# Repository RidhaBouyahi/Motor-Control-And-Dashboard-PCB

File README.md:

# Motor Control And Dashboard PCB
 
 This Dashboard PCB is developed to get data (position,temperature...) from sensors, control actuators and Dc Motor direction  and speed control using PWM .
All of these with the use of a touch panel screen connected to the board to make it easy for the user to operate and command everything with a simple touch.
The dimension of the PCB is 82.5*64 (mm)
It features : 
* Built-in H Bridge for speed and direction control.
* Reverse Current Protection Circuit.
* AVR-SPI Programmer. 
* UART for serial communications. 
* 4 digital and 5 Analog pins.

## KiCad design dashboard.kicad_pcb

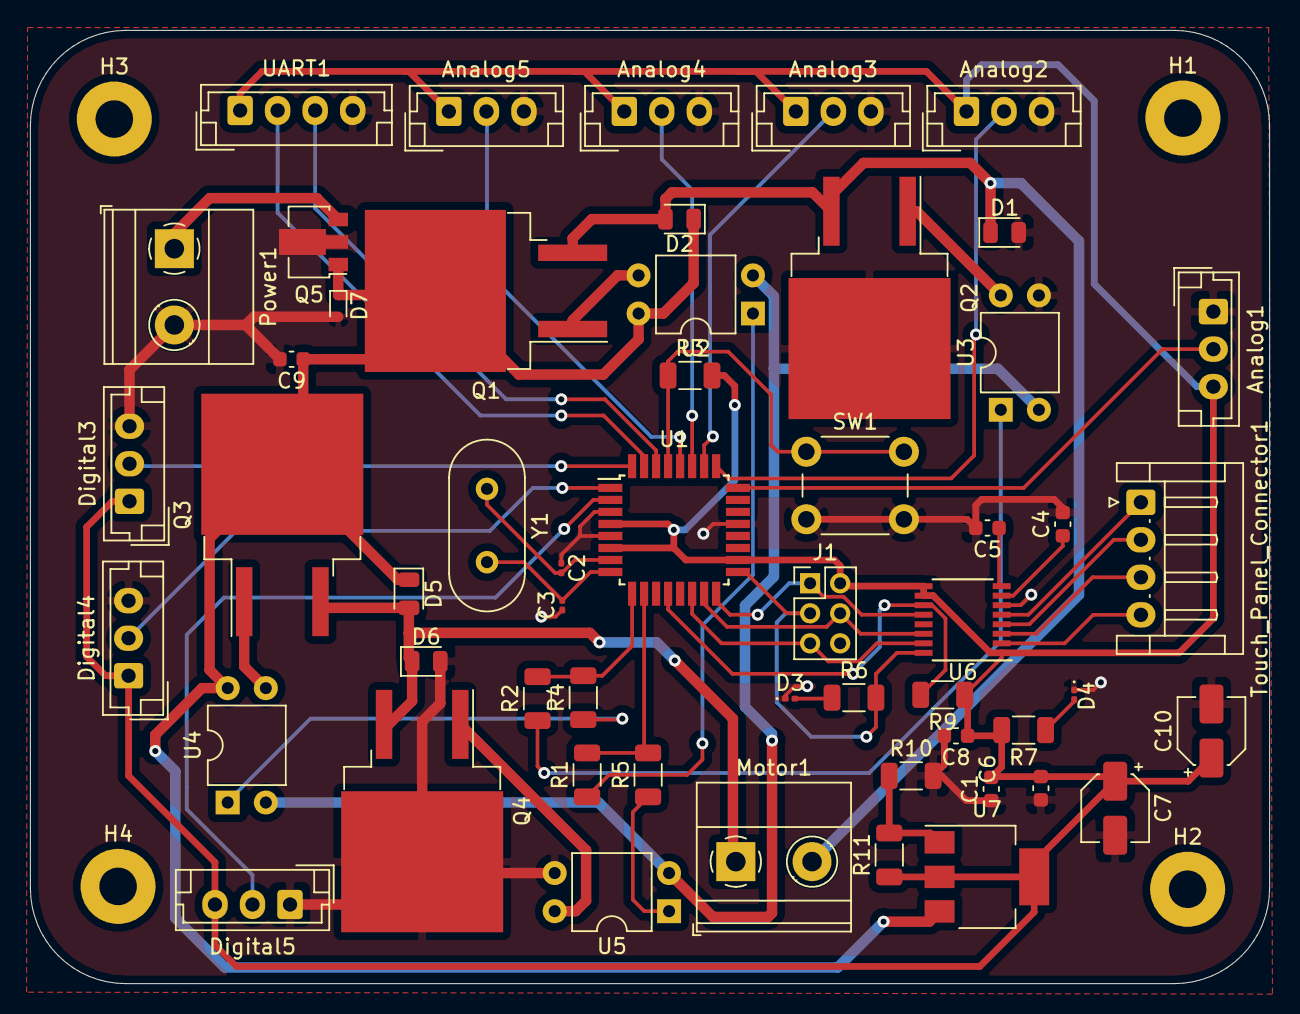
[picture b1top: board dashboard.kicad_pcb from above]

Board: 2 copper layers, 82.5 x 63.5 mm, 58 parts (0 on the bottom side), 44 nets.

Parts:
Analog1: ap1; JST_EH_B3B-EH-A_1x03_P2.50mm_Vertical
Analog2: ap2; JST_EH_B3B-EH-A_1x03_P2.50mm_Vertical
Analog3: ap3; JST_EH_B3B-EH-A_1x03_P2.50mm_Vertical
Analog4: ap4; JST_EH_B3B-EH-A_1x03_P2.50mm_Vertical
Analog5: ap5; JST_EH_B3B-EH-A_1x03_P2.50mm_Vertical
C1, C4, C5, C6, C8: 100nF; C_0603_1608Metric
C2, C3: 23pF; C_0201_0603Metric
C7: 10uF; CP_Elec_4x3
C9: 110nF; C_0603_1608Metric
C10: 180uF; CP_Elec_4x3
D1, D2, D5, D6: 1N4001; D_0805_2012Metric
D3, D4: LED; LED_0201_0603Metric
D7: D_Zener_Small; D_SC-80
Digital3: dp3; JST_EH_B3B-EH-A_1x03_P2.50mm_Vertical
Digital4: dp4; JST_EH_B3B-EH-A_1x03_P2.50mm_Vertical
Digital5: dp5; JST_EH_B3B-EH-A_1x03_P2.50mm_Vertical
H1, H2, H3, H4: MountingHole; MountingHole_2.5mm_Pad
J1: AVR-ISP-6; PinHeader_2x03_P2.00mm_Vertical
Motor1: Motor; TerminalBlock_Phoenix_MKDS-1,5-2-5.08_1x02_P5.08mm_Horizont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
Power1: Power; TerminalBlock_Phoenix_MKDS-1,5-2-5.08_1x02_P5.08mm_Horizont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
Q1, Q3: TIP122; TO-263-2
Q2, Q4: TIP127; TO-263-2
Q5: TP0610L; SOT-89-3
R1, R2, R4, R5: 1K2; R_1206_3216Metric
R3, R10: 10k; R_1206_3216Metric
R6, R7: 1k; R_1206_3216Metric
R9: 100k; R_1206_3216Metric
R11: 3k3; R_1206_3216Metric
SW1: SW_Push; SW_PUSH_6mm
Touch_Panel_Connector1: Touch Panel; JST_EH_S4B-EH_1x04_P2.50mm_Horizontal
U1: ATmega328-AU; TQFP-32_7x7mm_P0.8mm
U2, U3, U4, U5: EL817; DIP-4_W7.62mm
U6: ADS7843E; SSOP-16_3.9x4.9mm_P0.635mm
U7: LM317_SOT-223; SOT-223-3_TabPin2
UART1: UART; JST_EH_B4B-EH-A_1x04_P2.50mm_Vertical
Y1: 16MHz; Crystal_HC49-4H_Vertical

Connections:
+5: Analog1.3, Analog2.1, Analog3.1, Analog4.1, Analog5.1, C1.2, C6.1, C7.1, C8.1, C10.1, Digital3.1, Digital4.1, Digital5.3, J1.2, R3.2, R7.2, R9.1, R11.1, U1.4, U1.6, U1.18, U6.1, U6.9, U6.10, U7.2, UART1.1
+24V: C9.1, D2.1, D5.1, D7.1, Q1.2, Q3.2, Q5.1, U2.4, U4.4, U7.3
AP1: Analog1.2, U1.24
AP2: Analog2.2, U1.25
AP3: Analog3.2, U1.26
AP4: Analog4.2, U1.27
AP5: Analog5.2, U1.28
CLK: J1.3, R6.2, U1.17, U6.16
DP3: Digital3.2, U1.32
DP4: Digital4.2, U1.1
DP5: Digital5.2, U1.2
GND: Analog1.1, Analog2.3, Analog3.3, Analog4.3, Analog5.3, C1.1, C2.1, C3.1, C4.2, C5.2, C6.2, C7.2, C8.2, C9.2, C10.2, D1.2, D3.1, D4.1, D6.2, D7.2, Digital3.3, Digital4.3, Digital5.1, J1.6, Power1.2, Q2.2, Q4.2, Q5.2, R10.2, SW1.2, U1.3, U1.5, U1.21, U3.3, U5.3, U6.6, UART1.4
GNDPWR: U2.2, U3.2, U4.2, U5.2
INTERRUPT: R9.2, U1.12, U6.11
M+: D1.1, D2.2, Motor1.2, Q1.3, Q2.3
M-: D5.2, D6.1, Motor1.1, Q3.3, Q4.3
MISO: J1.1, U1.16, U6.12
MOSI: J1.4, U1.15, U6.14
unnamed: C2.2, U1.7, Y1.1
unnamed: C3.2, U1.8, Y1.2
unnamed: C4.1, U6.7
unnamed: C5.1, U6.8
unnamed: D3.2, R6.1
unnamed: D4.2, R7.1
unnamed: Power1.1, Q5.3
unnamed: Q1.1, U2.3
unnamed: Q2.1, U3.4
unnamed: Q3.1, U4.3
unnamed: Q4.1, U5.4
unnamed: R1.1, U2.1
unnamed: R2.1, U3.1
unnamed: R4.1, U4.1
unnamed: R5.1, U5.1
unnamed: R10.1, R11.2, U7.1
PWM0: R1.2, R5.2, U1.10
PWM1: R2.2, R4.2, U1.9
RST: R3.1, SW1.1, U1.29
RX: U1.30, UART1.3
TX: U1.31, UART1.2
X+: Touch_Panel_Connector1.4, U6.2
X-: Touch_Panel_Connector1.2, U6.4
Y+: Touch_Panel_Connector1.3, U6.3
Y-: Touch_Panel_Connector1.1, U6.5
~SS: J1.5, U1.14, U6.15

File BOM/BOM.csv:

Id;Symbol;Reference;Units;Part Value
1;UART1;JST_EH_B4B-EH-A_1x04_P2.50mm_Vertical;1;UART
2;H4,H3,H2,H1;MountingHole_2.5mm_Pad;4;MountingHole
3;Analog5;JST_EH_B3B-EH-A_1x03_P2.50mm_Vertical;1;ap5
4;Digital5;JST_EH_B3B-EH-A_1x03_P2.50mm_Vertical;1;dp5
5;Analog4;JST_EH_B3B-EH-A_1x03_P2.50mm_Vertical;1;ap4
6;Digital4;JST_EH_B3B-EH-A_1x03_P2.50mm_Vertical;1;dp4
7;Analog3;JST_EH_B3B-EH-A_1x03_P2.50mm_Vertical;1;ap3
8;Digital3;JST_EH_B3B-EH-A_1x03_P2.50mm_Vertical;1;dp3
9;Analog2;JST_EH_B3B-EH-A_1x03_P2.50mm_Vertical;1;ap2
10;Analog1;JST_EH_B3B-EH-A_1x03_P2.50mm_Vertical;1;ap1
11;Y1;Crystal_HC49-4H_Vertical;1;16MHz
12;U7;SOT-223-3_TabPin2;1;LM317_SOT-223
13;U6;SSOP-16_3.9x4.9mm_P0.635mm;1;ADS7843E
14;U5,U4,U3,U2;DIP-4_W7.62mm;4;EL817
15;U1;TQFP-32_7x7mm_P0.8mm;1;ATmega328-AU
16;SW1;SW_PUSH_6mm;1;SW_Push
17;R11;R_1206_3216Metric;1;3k3
18;R10,R3;R_1206_3216Metric;2;10k
19;R9;R_1206_3216Metric;1;100k
20;R7,R6;R_1206_3216Metric;2;1k
21;R5,R4,R2,R1;R_1206_3216Metric;4;1K2
22;Q5;SOT-89-3;1;TP0610L
23;Q4,Q2;TO-263-2;2;TIP127
24;Q3,Q1;TO-263-2;2;TIP122
25;Touch_Panel_Connector1;JST_EH_S4B-EH_1x04_P2.50mm_Horizontal;1;Touch Panel
26;Power1;TerminalBlock_Phoenix_MKDS-1,5-2-5.08_1x02_P5.08mm_Horizontal;1;Power
27;Motor1;TerminalBlock_Phoenix_MKDS-1,5-2-5.08_1x02_P5.08mm_Horizontal;1;Motor
28;J1;PinHeader_2x03_P2.00mm_Vertical;1;AVR-ISP-6
29;D7;D_SC-80;1;D_Zener_Small
30;D6,D5,D2,D1;D_0805_2012Metric;4;1N4001
31;D4,D3;LED_0201_0603Metric;2;LED
32;C10;CP_Elec_4x3;1;180uF
33;C9;C_0603_1608Metric;1;110nF
34;C8,C6,C5,C4,C1;C_0603_1608Metric;5;100nF
35;C7;CP_Elec_4x3;1;10uF
36;C3,C2;C_0201_0603Metric;2;23pF

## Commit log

2021-09-25 Add Project Files
